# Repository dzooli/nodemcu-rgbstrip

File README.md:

# nodemcu-rgbstrip

This project is a quick study for home automation with Domoticz, NodeMCU WiFi and an RGB LED strip.

## Control an RGB Led strip with NodeMCU using Domoticz RGB Dimmer controller

### HW Components

- Raspberry Pi3
- NodeMCU
- Transistors
- Voltage regulators
- Resistances
- RGB LED strip

### SW Components

- IDE: PlatformIO
- ESP8266 Board family for Arduino
- WiFi AP (currently a Raspberry Pi3)
- WifiManager library for Arduino
- Domoticz on the RPi3

[Details here](https://github.com/dzooli/nodemcu-rgbstrip/blob/master/doc/devlog.md)

## License

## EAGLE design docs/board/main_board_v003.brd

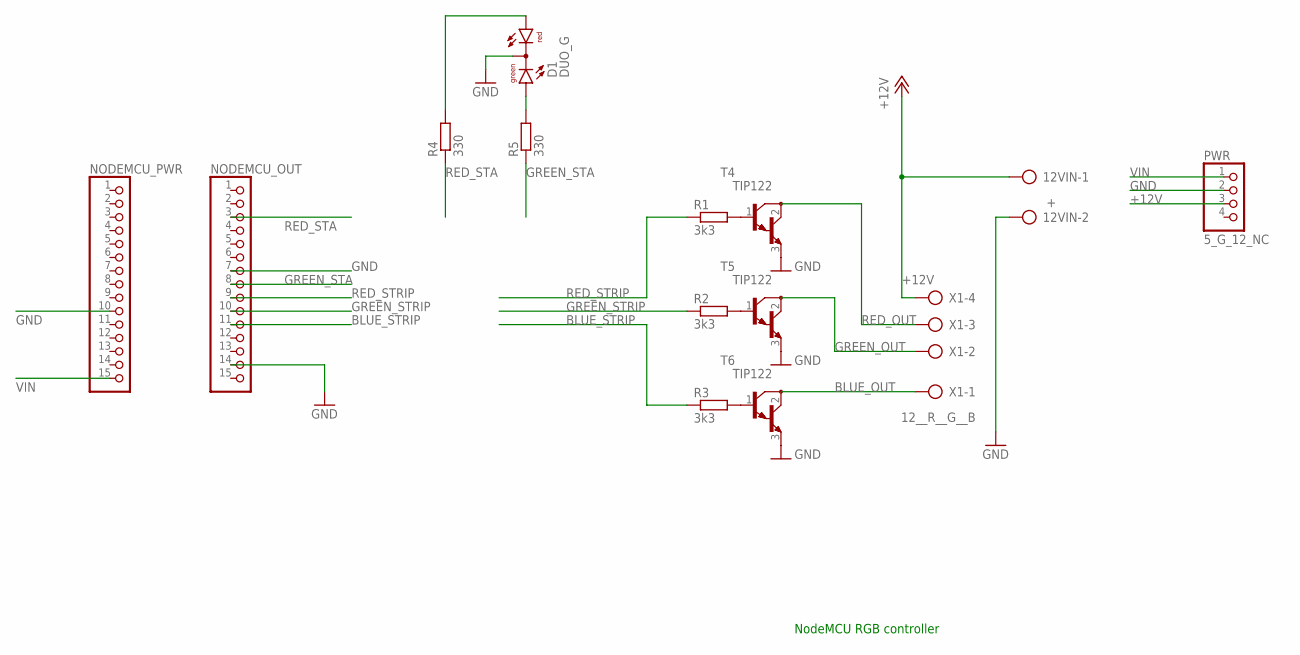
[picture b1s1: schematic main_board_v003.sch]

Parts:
12VIN: +; AK500/2-H
D1: DUO_G; DUOLED2X5
NODEMCU_OUT: PINHD-1X15; 1X15
NODEMCU_PWR: PINHD-1X15; 1X15
PWR: 5_G_12_NC; 1X04
R1, R2, R3: 3k3; 0207/10
R4, R5: 330; 0207/10
T4, T5, T6: TIP122; TO220
X1: 12__R__G__B; AK500/4-H

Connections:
+12V: 12VIN.1, PWR.3, X1.4
BLUE_OUT: T6.2 (C), X1.1
BLUE_STRIP: NODEMCU_OUT.11, R3.1
GND: 12VIN.2, D1.K (C), NODEMCU_OUT.7, NODEMCU_OUT.14, NODEMCU_PWR.10, PWR.2, T4.3 (E), T5.3 (E), T6.3 (E)
GREEN_OUT: T5.2 (C), X1.2
GREEN_STA: NODEMCU_OUT.8, R5.1
GREEN_STRIP: NODEMCU_OUT.10, R2.1
unnamed: R1.2, T4.1 (B)
unnamed: R2.2, T5.1 (B)
unnamed: R3.2, T6.1 (B)
unnamed: D1.AR, R4.2
unnamed: D1.AG, R5.2
RED_OUT: T4.2 (C), X1.3
RED_STA: NODEMCU_OUT.3, R4.1
RED_STRIP: NODEMCU_OUT.9, R1.1
VIN: NODEMCU_PWR.15, PWR.1

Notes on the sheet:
NodeMCU RGB controller

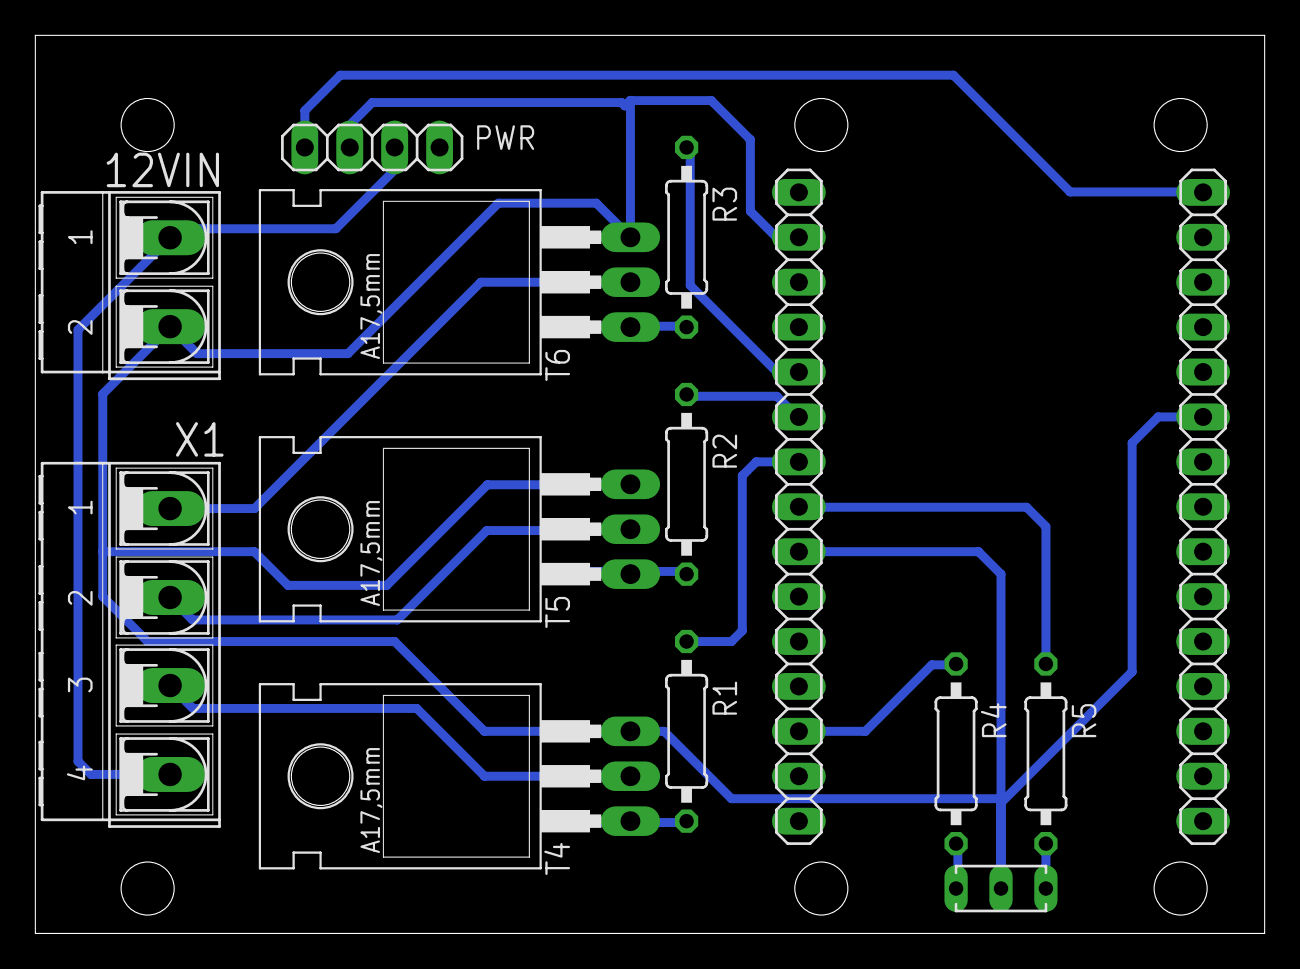
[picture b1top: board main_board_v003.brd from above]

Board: 2 copper layers, 69.5 x 50.8 mm, 14 parts (0 on the bottom side), 16 nets.

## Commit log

2017-07-30 readme updated
2017-07-31 Initial arduino script
2017-08-01 - wifi configuration portal - establish wifi connection - Next TODO: read credentials from a file in SPIFFS
2017-08-01 preparing to reset the NodeMCU
2017-08-02 config file handling
2017-08-03 config parser has been implemented
2017-08-21 output pin changed d1=red, d2=green, d3=(input on NodeMCU1 | flash button, d4=blue) and comments added
2017-08-23 beginning of the configuration saving
2017-08-27 saveConfigCallback has been finished
    We have to test it on the real environment
2017-08-27 captive portal and config save/load added
2017-08-31 strings to PROGMEM
2018-08-31 Automatic connection to a preconfigured AP is ok. Status LED handling macros. Status feedback with LEDs. MQTT parameter enrty on the captive portal.
2019-12-02 MQTT parameter length to constants, status led update on successful WiFI connection
2019-12-03 MQTT friendly name added
2020-01-29 MQTT payload parser implementation started. Added high resolution PWM routines
2020-01-29 MQTT payload parser started. MQTT connection ok with callback
2020-02-09 MQTT payload is filtered by the device's friendly name. Hi-res PWM has been removed.
2020-02-09 subscribeMQTT declaration fix
2020-02-12 Update README.md
    Added Domoticz related description
2020-02-12 Set theme jekyll-theme-architect
2020-03-11 added the comment for presentation purposes
2020-03-11 improvement ideas added
2020-03-12 added some documentation files
2020-03-12 custom scripts added
2020-03-23 Added Fritzing breadboard and Drawing.io HWSW design images and sources
2020-03-23 Cleanup and image embedding
2020-03-24 Added PWM output setup and switching OFF functionality. Just works.
2020-03-24 Added captive portal images
2020-03-24 Regenerated by marp
2020-03-24 Captive images added
2020-03-24 Pin layout changed to be more NodeMCU compatible
2020-03-25 blog entry update
2020-03-25 blog entry fixed
2020-04-07 breadboard update
2020-04-07 Devlog for blog version added
2020-04-10 Add license scan report and status
2020-04-10 blog version of devlog
2020-04-10 save state to EEPROM added
2020-04-11 devlog.md blog link fixed
2020-04-11 blog link fixed, some format fixes
2020-04-11 link to the details page added
2020-04-11 link typo fix
2022-12-20 moved to platformIO
2022-12-20 separated doc directory
2022-12-20 cleanup vscode remains
2022-12-20 moved to CPP and compile_command generation
2022-12-20 README formatting
2022-12-20 License restored
2022-12-20 using LitlleFS instead of SPIFFS
2022-12-20 Configured static analyzer
2022-12-20 ignore code-workspace
2022-12-20 moved to LittleFS and minor fixes
2022-12-20 clang compatibility fix
2022-12-20 PlatformIO-generated launch configuration
2022-12-20 ignore package files during static analysis
2022-12-21 Added SonarCloud badge
2022-12-21 GitHub Pages try
2022-12-21 ren to index.md
2022-12-21 theme change
2022-12-21 ren index.md
2022-12-21 rename to the new index
2022-12-21 removed EEPROM related pieces
2022-12-21 increased MQTT buffer size
2022-12-21 added upload port and monitor speed settings
2022-12-21 word dictionary update
2022-12-21 for debug messages
2022-12-21 easier debugging, status loading started, removed EEPROM deps
2022-12-26 separating macros and types
2022-12-26 project specific types
2022-12-26 reading cleanup
2022-12-26 cleanup and status file parsing addition
2022-12-26 updated commands for IntelliSense
2022-12-26 added unknown words
2022-12-26 updated .gitignore
2022-12-26 removed some debug info and added status save functionality
2022-12-26 hardcoded port removed
2022-12-26 added config files
2022-12-26 last status retrieval implementation
2022-12-26 sample status file
2022-12-27 selfTest() moved to here
2022-12-27 cleanup and pin layout changes
2022-12-27 project dir change
2022-12-27 constants separation
2022-12-27 WiFi related separation to another library (partial)
2022-12-27 cleanup for readability and cleaner code
2022-12-27 include path fixes
2022-12-27 wifi reconnection added
2022-12-27 wifi debug mode off
2022-12-28 exclude credentials
2023-01-07 updated compile commands
2023-03-25 added board plans
